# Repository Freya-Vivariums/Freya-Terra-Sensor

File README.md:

The **Freya Terra Sensor** is the control system's eyes and ears within the vivarium - the hardware that enables measurement of environmental conditions experienced by the inhabitants of the vivarium.

#### Measurement capabilities:
- Temperature
- Relative air humidity
- Barometric pressure
- Air quality (VOC)
- Ambient light (visible spectrum)
- UVA/UVB/UVC (spectral 220-400nm)

<br clear="right"/>

## Hardware
Designed with **[KiCad](https://www.kicad.org/download/)**, the Freya Terra Sensor's electronic hardware is a curated collection of high-end integrated circuit sensors for comprehensive environmental monitoring.

- Bosch **BME680** (**0x76**): Integrated environmental sensor combining **temperature**, **humidity**, **barometric pressure**, and VOC gas sensing for **air quality** monitoring. **[Datasheet](https://www.bosch-sensortec.com/media/boschsensortec/downloads/datasheets/bst-bme680-ds001.pdf)**
- Vishay **VEML6030** (**0x10**): High-accuracy **ambient light** sensor with spectral response matching the human eye for precise lux measurement and photoperiod management. **[Datasheet](https://www.vishay.com/docs/84366/veml6030.pdf)**
- ams OSRAM **AS7331** (**0x74**): Three-channel **spectral UV** sensor with separated UVA, UVB, and UVC detection for UV bulb monitoring and safety verification. **[Datasheet](https://look.ams-osram.com/m/1856fd2c69c35605/original/AS7331-Spectral-UVA-B-C-Sensor.pdf)**
- Microchip **MIC5225-3.3YM5**: The sensor module operates internally at 3.3V but accepts 5V input for improved noise immunity over longer cable runs. The on-board voltage regulator provides clean 3.3V power to all sensor ICs, while a bi-directional level shifter handles I²C communication between the 5V bus and 3.3V sensors.
- The **JST PH 2.0mm 4-Pin connector** allows for easy replacement of the board.

> [!NOTE]  
> The PCB is finished with a coating for resisting the humid conditions.

## Enclosure

The sensor's enclosure is designed in **[FreeCAD](https://www.freecad.org/downloads.php?lang=en)**. It protects the sensitive equipment from the challenges of the environment within the vivarium. The **quartz tube** provides full-spectrum light transparency for spectral measurements while **mesh-filtered ventilation** in the end caps enables air exchange for sensing. The internal holder positions the PCB and facilitates assembly.

<br clear="right"/>

## Software
The sensor driver is a TypeScript/Node.js application that runs as a systemd service on Linux/Debian systems. It provides sensor readings via D-Bus for integration with the Freya Vivarium Control System Node-RED application.

#### Installation
When installing the Freya system, the sensor driver is automatically installed. For manual installation:

```bash
wget -O install.sh https://github.com/Freya-Vivariums/Freya-terra-sensor/releases/latest/download/install.sh
chmod +x ./install.sh
sudo ./install.sh
```

The service runs automatically and can be monitored with:
```bash
systemctl status freya.sensor.terra.service
journalctl -u freya.sensor.terra.service -f
```

#### D-Bus Interface
Applications interact with the sensor via D-Bus on the system bus:
- **Service:** `freya.sensor.terra`
- **Path:** `/freya/sensor/terra`
- **Signals:** `measurement(variable: string, value: string)` - Emits readings for temperature, humidity, pressure, light, UVA, UVB, and UVC

## License & Collaboration
**Copyright© 2024-2026 Sanne 'SpuQ' Santens**. The hardware and enclosure are released under the [**CERN OHL-W**](Hardware/LICENSE.txt) license. The software is released under the [**GNU GPL-3.0**](Software/LICENSE.txt) license. [Trademark rules](https://github.com/Freya-Vivariums/.github/blob/main/brand/Freya_Trademark_Rules_and_Guidelines.md) apply to the Freya™ brand.

### Collaboration

If you'd like to contribute to this project, please follow these guidelines:
1. Fork the repository and create your branch from `main`.
2. Make your changes and ensure they adhere to the project's design style and conventions.
3. Test your changes thoroughly.
4. Ensure your commits are descriptive and well-documented.
5. Open a pull request, describing the changes you've made and the problem or feature they address.

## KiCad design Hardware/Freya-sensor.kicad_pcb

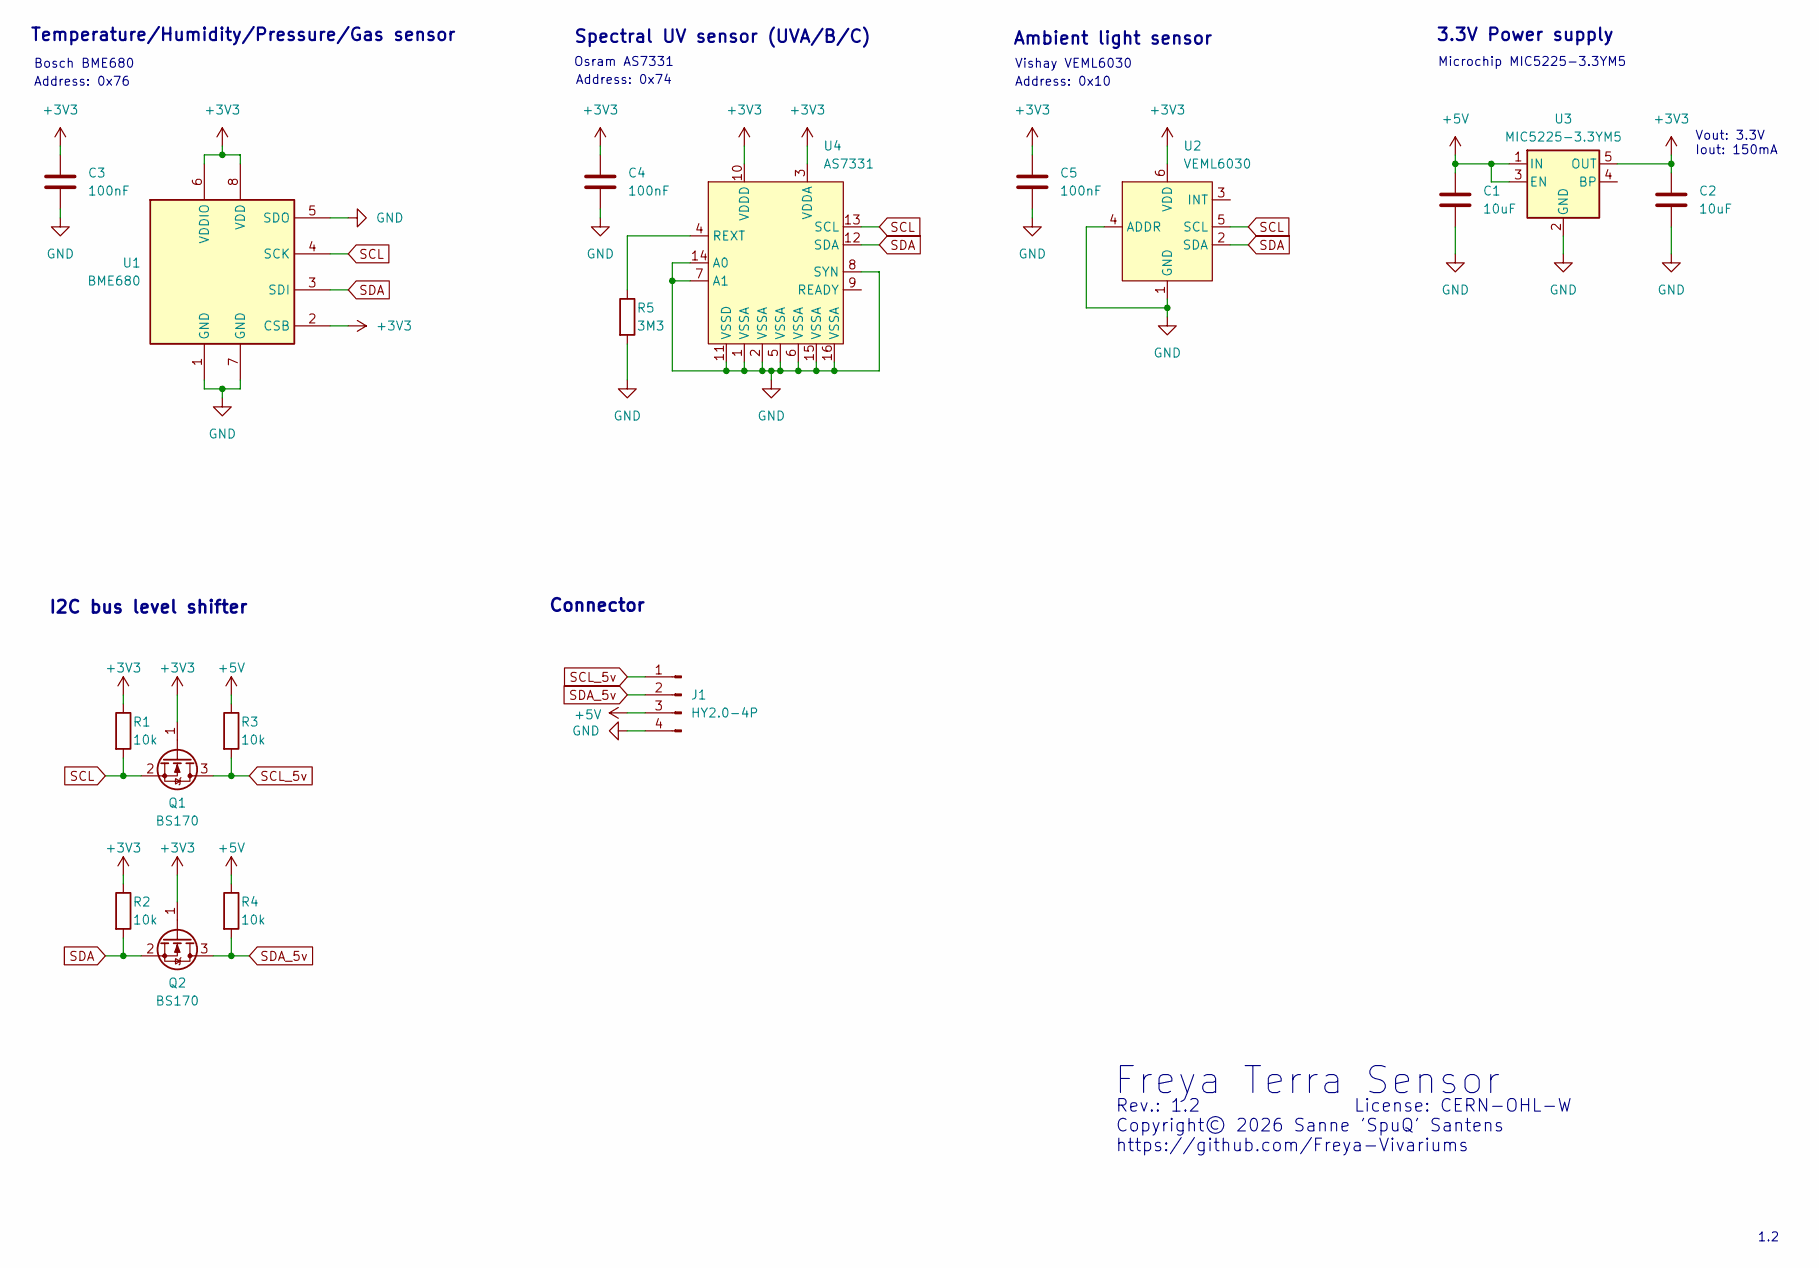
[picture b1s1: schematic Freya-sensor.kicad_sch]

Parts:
C1, C2: 10uF; C_0805_2012Metric
C3, C4, C5: 100nF; C_0805_2012Metric
J1: HY2.0-4P; Grove_SMD_right_angle
Q1, Q2: BS170; SOT-23
R1, R2, R3, R4: 10k; R_0805_2012Metric
R5: 3M3; R_0805_2012Metric
U1: BME680
U2: VEML6030
U3: MIC5225-3.3YM5; SOT-23-5
U4: AS7331; Osram_AS7331

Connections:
+3V3: C2.1, C3.1, C4.1, C5.1, Q1.1 (G), Q2.1 (G), R1.1, R2.1, U1.2 (CSB), U1.6 (VDDIO), U1.8 (VDD), U2.6 (VDD), U3.5 (OUT), U4.3 (VDDA), U4.10 (VDDD)
+5V: C1.1, J1.3, R3.1, R4.1, U3.1 (IN), U3.3 (EN)
GND: C1.2, C2.2, C3.2, C4.2, C5.2, J1.4, J1.5, R5.2, U1.1 (GND), U1.5 (SDO), U1.7 (GND), U2.1 (GND), U2.4 (ADDR), U3.2 (GND), U4.1 (VSSA), U4.2 (VSSA), U4.5 (VSSA), U4.6 (VSSA), U4.7 (A1), U4.8 (SYN), U4.11 (VSSD), U4.14 (A0), U4.15 (VSSA), U4.16 (VSSA)
unnamed: R5.1, U4.4 (REXT)
SCL: Q1.2 (S), R1.2, U1.4 (SCK), U2.5 (SCL), U4.13 (SCL)
SCL_5v: J1.1, Q1.3 (D), R3.2
SDA: Q2.2 (S), R2.2, U1.3 (SDI), U2.2 (SDA), U4.12 (SDA)
SDA_5v: J1.2, Q2.3 (D), R4.2

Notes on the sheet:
Spectral UV sensor (UVA/B/C)
Bosch BME680
Rev.: 1.2 License: CERN-OHL-W
3.3V Power supply
Vout: 3.3V Iout: 150mA
Address: 0x76
Connector
Microchip MIC5225-3.3YM5
Address: 0x74
https://github.com/Freya-Vivariums
I2C bus level shifter
Copyright© 2026 Sanne 'SpuQ' Santens
Vishay VEML6030
Osram AS7331
Address: 0x10
Ambient light sensor
Freya Terra Sensor
1.2
Temperature/Humidity/Pressure/Gas sensor

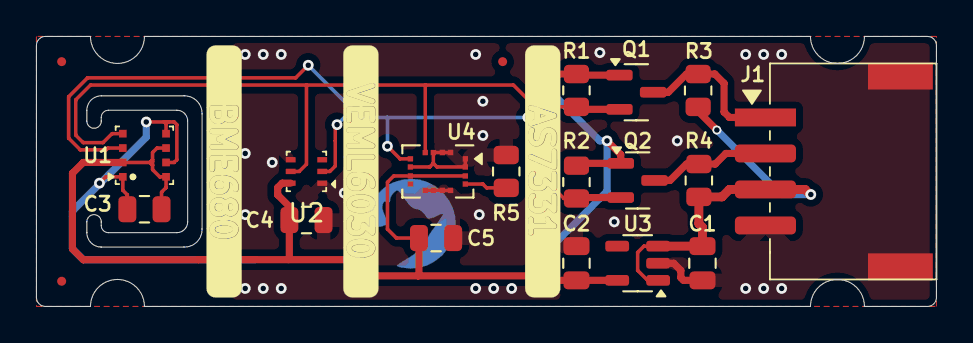
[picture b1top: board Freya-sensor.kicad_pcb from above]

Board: 2 copper layers, 50.0 x 15.0 mm, 17 parts (0 on the bottom side), 8 nets.

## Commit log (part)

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2026-02-10 Software: AS7331 driver improvements
2026-02-10 Software: VEML6030 auto range concept
2026-02-10 Software: Relative air quality implementation
2026-03-13 Update enclosure
2026-03-13 Update documentation
2026-03-16 Enclosure center corrections
2026-03-17 Enclosure: Center ventilation channel
2026-03-17 Enclosure: PCB cutout
2026-03-19 Enclosure: cable protector
2026-03-19 Sensor enclosure model update
2026-03-19 Documentation: Sensor rendering update
2026-03-24 Enclosure: assembly documentation
2026-03-25 Enclosure: included the bolts
2026-04-13 Enclosure: Mesh Mask
2026-04-16 Documentation: sensor rendering
2026-04-16 Enclosure coloring
2026-04-17 Documentation: Enclosure exploded image
2026-04-29 Driver: light precision
2026-04-29 Driver: auto-range implementation
2026-04-29 Driver: AS7331 auto-range implementation + bugfixes
2026-04-29 Driver: light sensor auto-range improvements
2026-04-29 Driver: deploy local
2026-05-29 Software: Node-RED node migration
2026-05-29 Software: Node Client
2026-05-29 Software: Node-RED nodes readme
2026-05-29 Software: Node-RED Sensor Measurement Node rename
2026-05-29 Software: system & dbus service name update
